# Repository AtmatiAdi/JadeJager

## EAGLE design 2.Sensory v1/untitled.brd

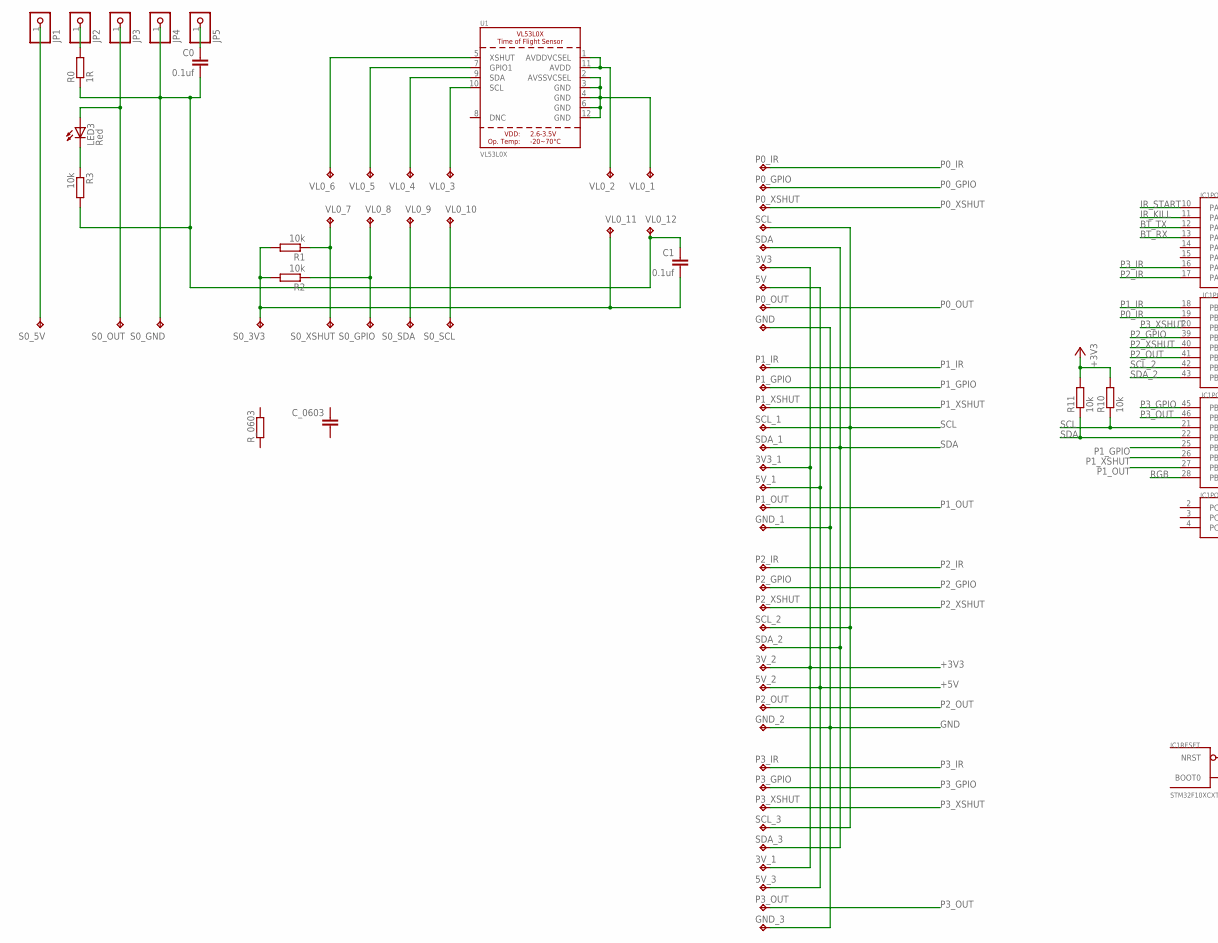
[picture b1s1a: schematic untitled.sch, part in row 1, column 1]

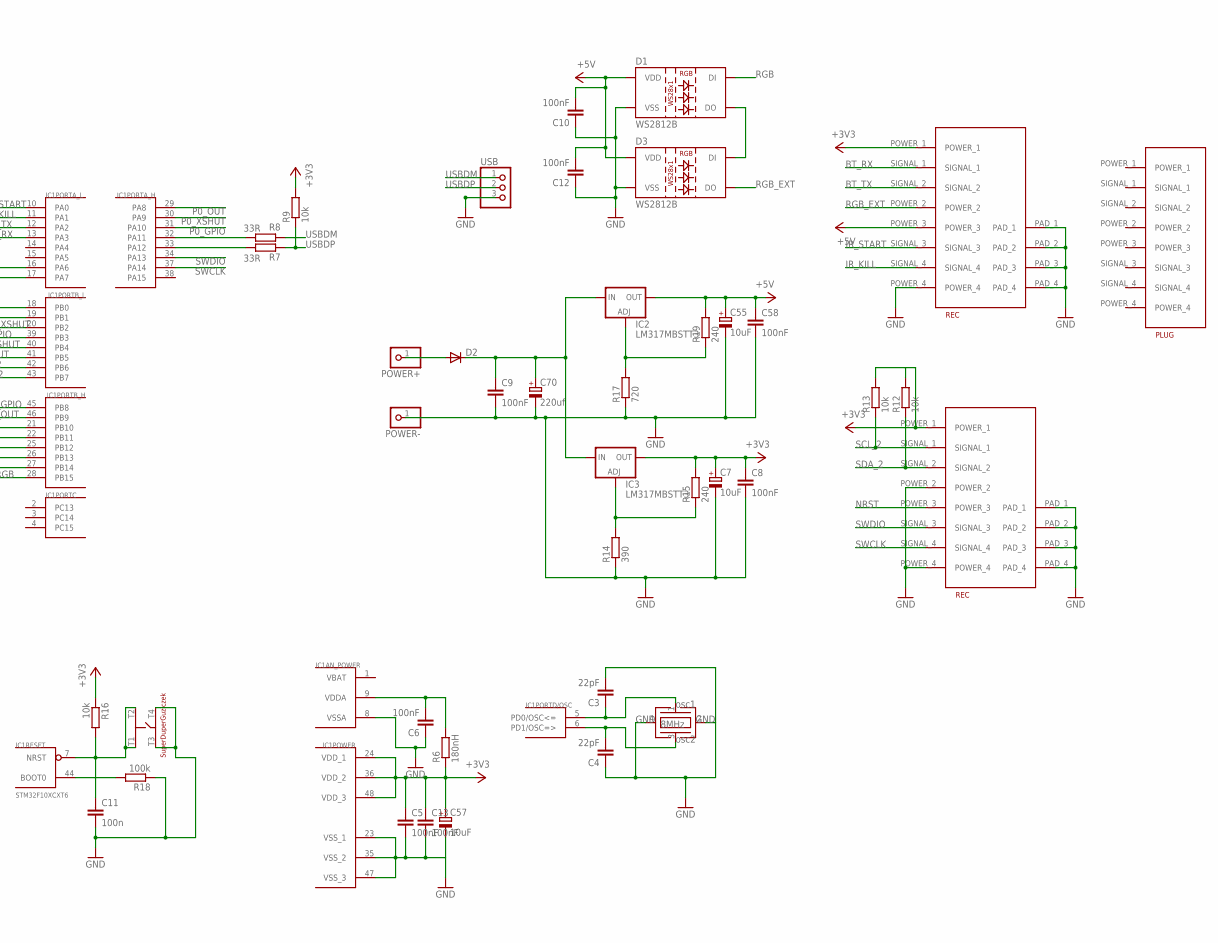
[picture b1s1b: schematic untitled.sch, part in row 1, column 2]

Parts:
3V3, 3V3_1, 3V_1, 3V_2, 5V, 5V_1, 5V_2, 5V_3: TPTP09SQ; TP09SQ
C0, C1: 0.1uf; C0603
C3, C4: 22pF; C0603
C5, C6, C8, C9, C10, C12, C13, C58: 100nF; C0603
C7, C55, C57: 10uF; SMC_A
C11: 100n; C0603
C70: 220uf; 150CLZ-0810
C_0603: C-EUC0603; C0603
D1, D3: WS2812B
D2: DIODE-DO214BA; DO214BA
GND: TPTP09SQ; TP09SQ
GND_1, GND_2, GND_3: TPTP09SQ; TP09SQ
IC1: STM32F10XCXT6; TQFP48
IC2, IC3: LM317MBSTT3; SOT223
JP1, JP2, JP3, JP4, JP5: PINHD-1X1; 1X01
LED3: Red; SML0603
P0_GPIO, P0_IR, P0_OUT, P0_XSHUT, P1_GPIO, P1_IR, P1_OUT, P1_XSHUT, P2_GPIO, P2_IR, P2_OUT, P2_XSHUT, P3_GPIO, P3_IR, P3_OUT, P3_XSHUT: TPTP09SQ; TP09SQ
POWER+: PINHD-1X1; 1X01
POWER-: PINHD-1X1; 1X01
R0: 1R; R0603
R1, R2, R3, R9, R10, R11, R12, R13, R16: 10k; R0603
R6: 180nH; R0603
R7, R8: 33R; R0603
R14: 390; R0603
R15, R19: 240; R0603
R17: 720; R0603
R18: 100k; R0603
R_0603: R-EU_R0603; R0603
S0_3V3, S0_5V, S0_GND, S0_GPIO, S0_OUT, S0_SCL, S0_SDA, S0_XSHUT: TPTP09SQ; TP09SQ
SCL: TPTP09SQ; TP09SQ
SCL_1, SCL_2, SCL_3: TPTP09SQ; TP09SQ
SDA: TPTP09SQ; TP09SQ
SDA_1, SDA_2, SDA_3: TPTP09SQ; TP09SQ
U1: VL53L0X; LGA12_ST
U$1, U$3: MOLEG_REC_8X0.4MM; REC
U$2: MOLEX_PLUG_8X0.4MM; PLUG
U$27: SUPER_DUPER_GUZICZEK
U$35: 8MHZ; SMD
USB: PINHD-1X3; 1X03
VL0_1, VL0_2, VL0_3, VL0_4, VL0_5, VL0_6, VL0_7, VL0_8, VL0_9, VL0_10, VL0_11, VL0_12: TPTP09SQ; TP09SQ

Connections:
+3V3: 3V3.TP, 3V3_1.TP, 3V_1.TP, 3V_2.TP, C5.1, C7.+, C8.1, C13.1, C57.+, IC1.24 (VDD_1), IC1.36 (VDD_2), IC1.48 (VDD_3), IC3.4 (OUT), R6.1, R9.2, R10.2, R11.2, R12.2, R13.2, R15.2, R16.1, U$1.POWER_1, U$3.POWER_1
+5V: 5V.TP, 5V_1.TP, 5V_2.TP, 5V_3.TP, C10.2, C12.2, C55.+, C58.1, D1.1 (VDD), D3.1 (VDD), IC2.4 (OUT), R19.2, U$1.POWER_3
BT_RX: IC1.13 (PA3), U$1.SIGNAL_1
BT_TX: IC1.12 (PA2), U$1.SIGNAL_2
GND: C3.2, C4.1, C5.2, C6.1, C7.-, C8.2, C9.2, C10.1, C11.2, C12.1, C13.2, C55.-, C57.-, C58.2, C70.-, D1.3 (VSS), D3.3 (VSS), GND.TP, GND_1.TP, GND_2.TP, GND_3.TP, IC1.8 (VSSA), IC1.23 (VSS_1), IC1.35 (VSS_2), IC1.47 (VSS_3), POWER-.1, R14.1, R17.1, R18.1, U$1.PAD_1, U$1.PAD_2, U$1.PAD_3, U$1.PAD_4, U$1.POWER_4, U$3.PAD_1, U$3.PAD_2, U$3.PAD_3, U$3.PAD_4, U$3.POWER_2, U$3.POWER_4, U$27.T3, U$27.T4, U$35.2 (GND2), U$35.4 (GND1), USB.3
GND_TOFIK: U1.2 (AVSSVCSEL), U1.3 (GND), U1.4 (GND), U1.6 (GND), U1.12 (GND), VL0_1.TP
IR_KILL: IC1.11 (PA1), U$1.SIGNAL_4
IR_START: IC1.10 (PA0), U$1.SIGNAL_3
unnamed: JP2.1, R0.2
unnamed: C0.1, JP5.1
unnamed: LED3.C, R3.1
unnamed: U1.10 (SCL), VL0_3.TP
unnamed: U1.1 (AVDDVCSEL), U1.11 (AVDD), VL0_2.TP
unnamed: U1.9 (SDA), VL0_4.TP
unnamed: U1.7 (GPIO1), VL0_5.TP
unnamed: U1.5 (XSHUT), VL0_6.TP
unnamed: IC3.1 (ADJ), R14.2, R15.1
unnamed: D2.A, POWER+.1
unnamed: C9.1, C70.+, D2.C, IC2.3 (IN), IC3.3 (IN)
unnamed: IC2.1 (ADJ), R17.2, R19.1
unnamed: IC1.44 (BOOT0), R18.2
unnamed: D1.2 (DO), D3.4 (DI)
unnamed: IC1.33 (PA12), R7.2
unnamed: IC1.32 (PA11), R8.2
unnamed: C6.2, IC1.9 (VDDA), R6.2
unnamed: C3.1, IC1.5 (PD0/OSC<=), U$35.1
unnamed: C4.2, IC1.6 (PD1/OSC=>), U$35.3 (2)
NRST: C11.1, IC1.7 (NRST), R16.2, U$3.POWER_3, U$27.T1, U$27.T2
P0_GPIO: IC1.31 (PA10), P0_GPIO.TP
P0_IR: IC1.19 (PB1), P0_IR.TP
P0_OUT: IC1.29 (PA8), P0_OUT.TP
P0_XSHUT: IC1.30 (PA9), P0_XSHUT.TP
P1_GPIO: IC1.25 (PB12), P1_GPIO.TP
P1_IR: IC1.18 (PB0), P1_IR.TP
P1_OUT: IC1.27 (PB14), P1_OUT.TP
P1_XSHUT: IC1.26 (PB13), P1_XSHUT.TP
P2_GPIO: IC1.39 (PB3), P2_GPIO.TP
P2_IR: IC1.17 (PA7), P2_IR.TP
P2_OUT: IC1.41 (PB5), P2_OUT.TP
P2_XSHUT: IC1.40 (PB4), P2_XSHUT.TP
P3_GPIO: IC1.45 (PB8), P3_GPIO.TP
P3_IR: IC1.16 (PA6), P3_IR.TP
P3_OUT: IC1.46 (PB9), P3_OUT.TP
P3_XSHUT: IC1.20 (PB2), P3_XSHUT.TP
RGB: D1.4 (DI), IC1.28 (PB15)
RGB_EXT: D3.2 (DO), U$1.POWER_2
S0_3V3: C1.2, R1.2, R2.2, S0_3V3.TP, VL0_11.TP
S0_5V: JP1.1, S0_5V.TP
S0_GND: C0.2, C1.1, JP4.1, R0.1, R3.2, S0_GND.TP, VL0_12.TP
S0_GPIO: R2.1, S0_GPIO.TP, VL0_8.TP
S0_OUT: JP3.1, LED3.A, S0_OUT.TP
S0_SCL: S0_SCL.TP, VL0_10.TP
S0_SDA: S0_SDA.TP, VL0_9.TP
S0_XSHUT: R1.1, S0_XSHUT.TP, VL0_7.TP
SCL: IC1.21 (PB10), R10.1, SCL.TP, SCL_1.TP, SCL_2.TP, SCL_3.TP
SCL_2: IC1.42 (PB6), R13.1, U$3.SIGNAL_1
SDA: IC1.22 (PB11), R11.1, SDA.TP, SDA_1.TP, SDA_2.TP, SDA_3.TP
SDA_2: IC1.43 (PB7), R12.1, U$3.SIGNAL_2
SWCLK: IC1.37 (PA14), U$3.SIGNAL_4
SWDIO: IC1.34 (PA13), U$3.SIGNAL_3
USBDM: R8.1, USB.1
USBDP: R7.1, R9.1, USB.2
VBAT: IC1.1 (VBAT)

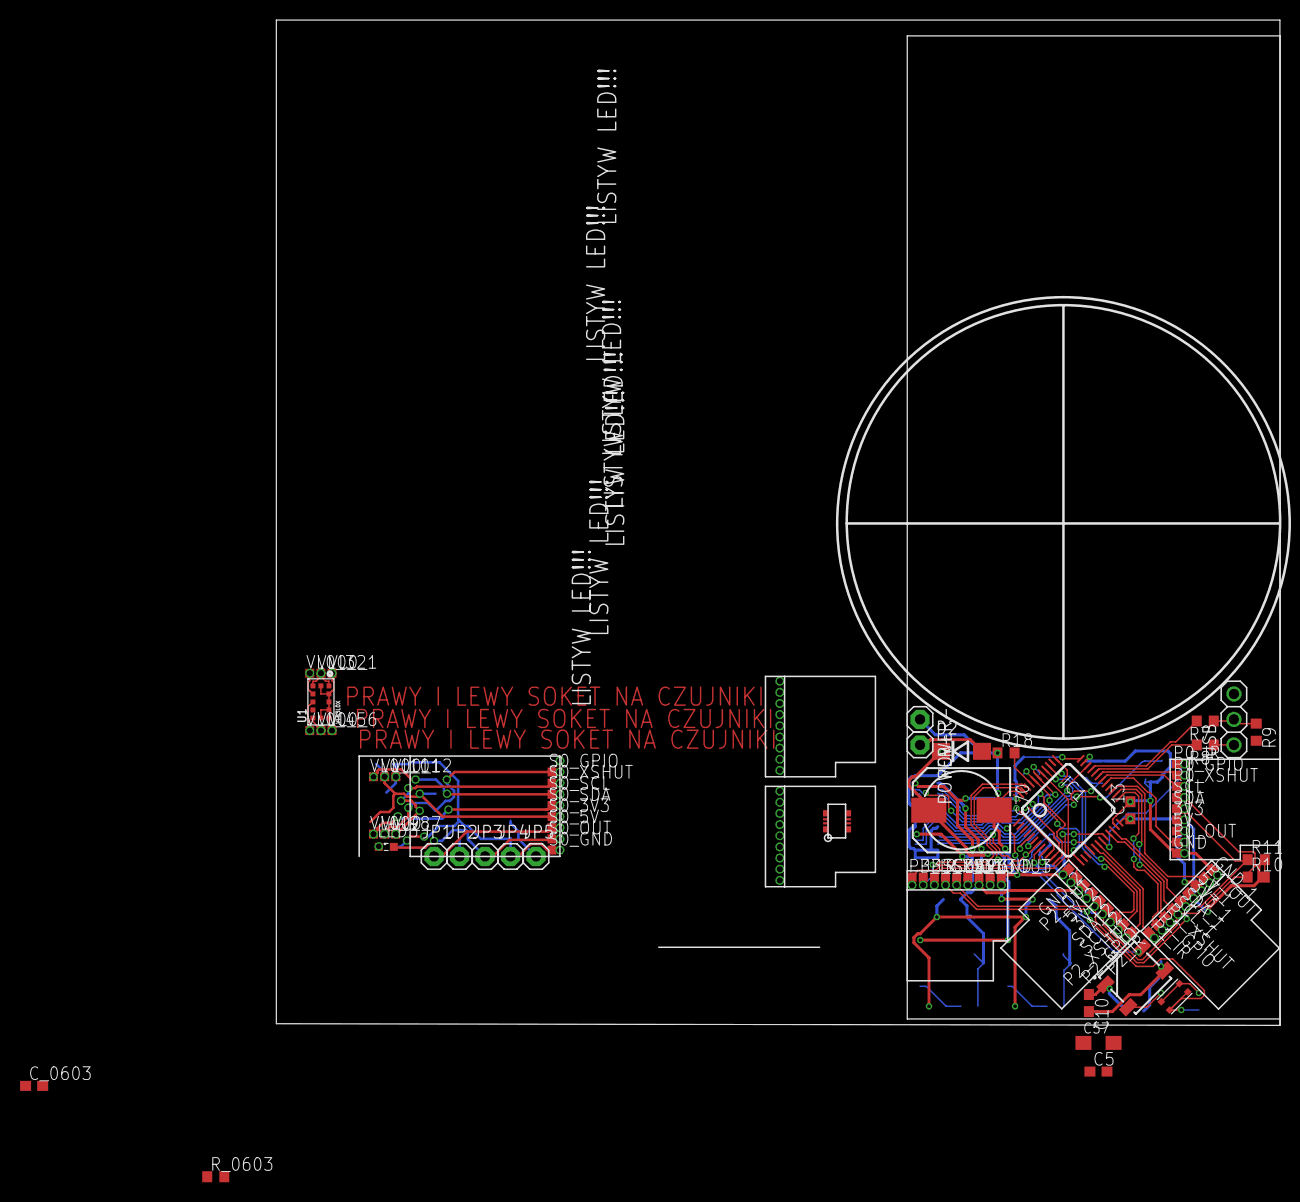
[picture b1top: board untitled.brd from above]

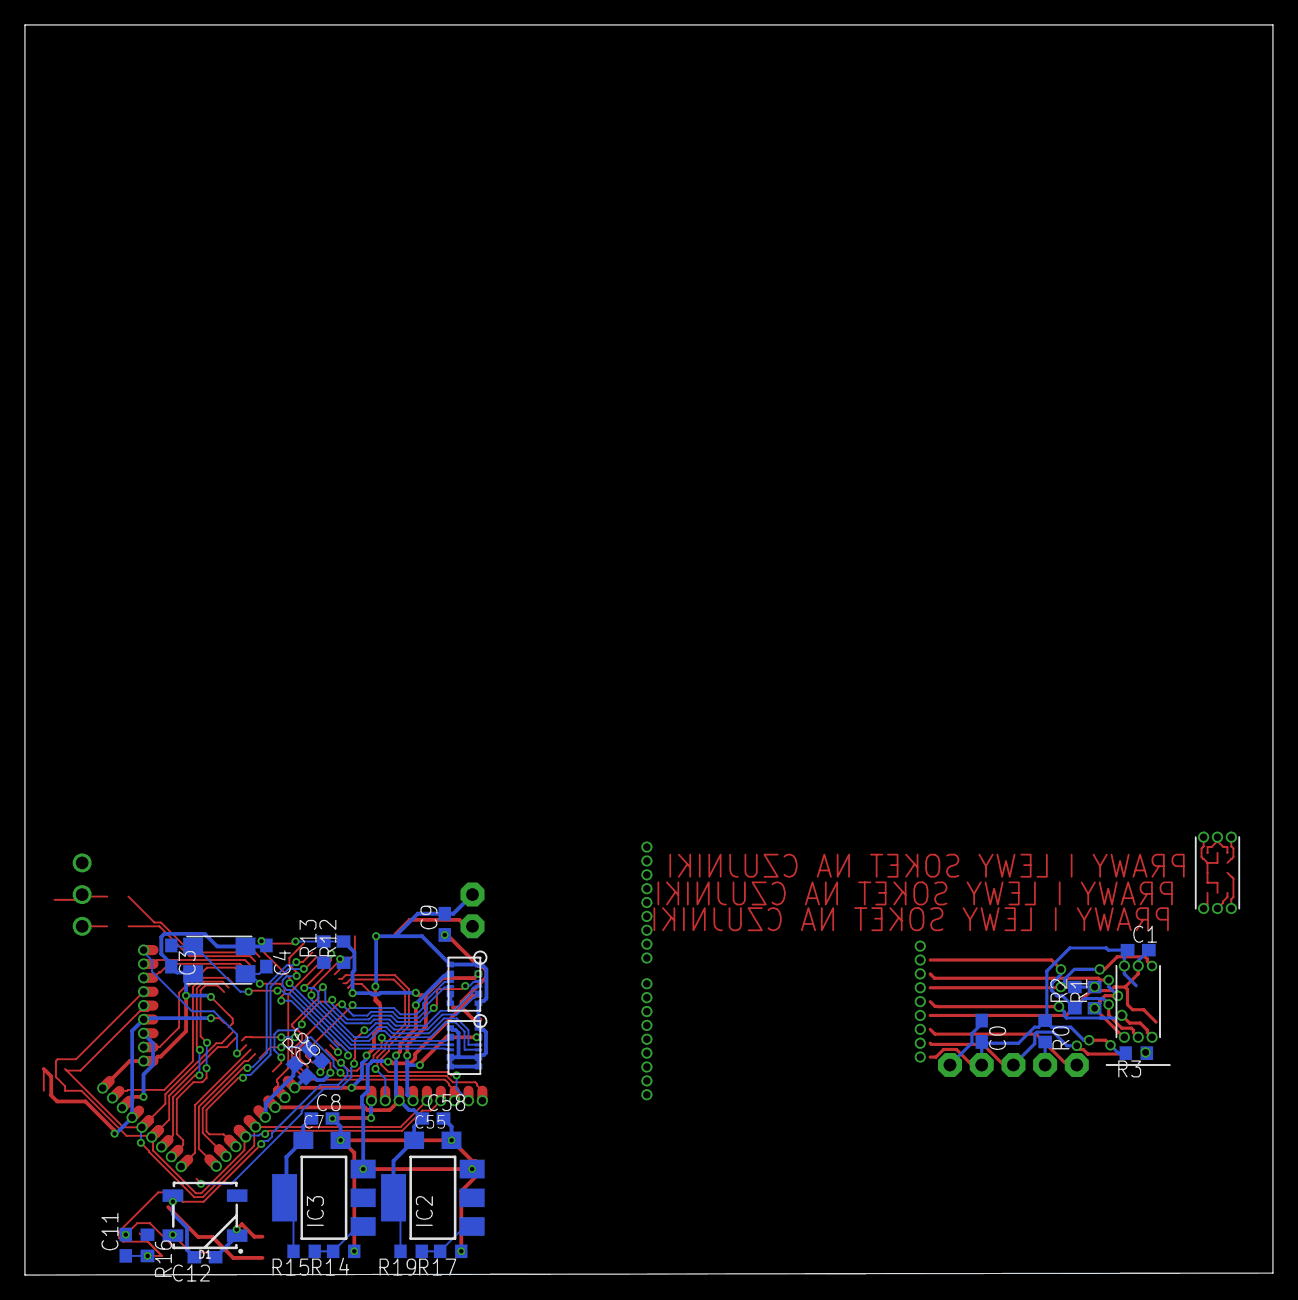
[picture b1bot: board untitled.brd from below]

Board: 2 copper layers, 100.0 x 100.2 mm, 114 parts (30 on the bottom side), 62 nets.

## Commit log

2020-05-14 Wprowadzono projekt

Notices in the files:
parts and their libraries:
microbuilder: This work is placed in the public domain, and may be freely used for commercial and non-commercial work with the following conditions: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
SparkFun-LED: Licensing: Creative Commons ShareAlike 4.0 International - https://creativecommons.org/licenses/by-sa/4.0
